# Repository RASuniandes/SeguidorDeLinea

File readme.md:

# Seguidor de linea
## Equipo 2024-1:
- Sergio Mora (SerAle25)
- Mateo López (Mateo-Lopez83)
- Alejandro Alvernia (AlejandroAAL)
- Laura Avelino (Lauraavelin)
- Valentina Romo ()
- Juan Felipe Ángulo (JuanFelipeAngulo)
- Mariana Vanoy (i4d1luc)
En rotación Valentina Arenas (Con interés de aprender temas de diseño mecánico e IMEC)

**Este es el equipo para 2024-1**

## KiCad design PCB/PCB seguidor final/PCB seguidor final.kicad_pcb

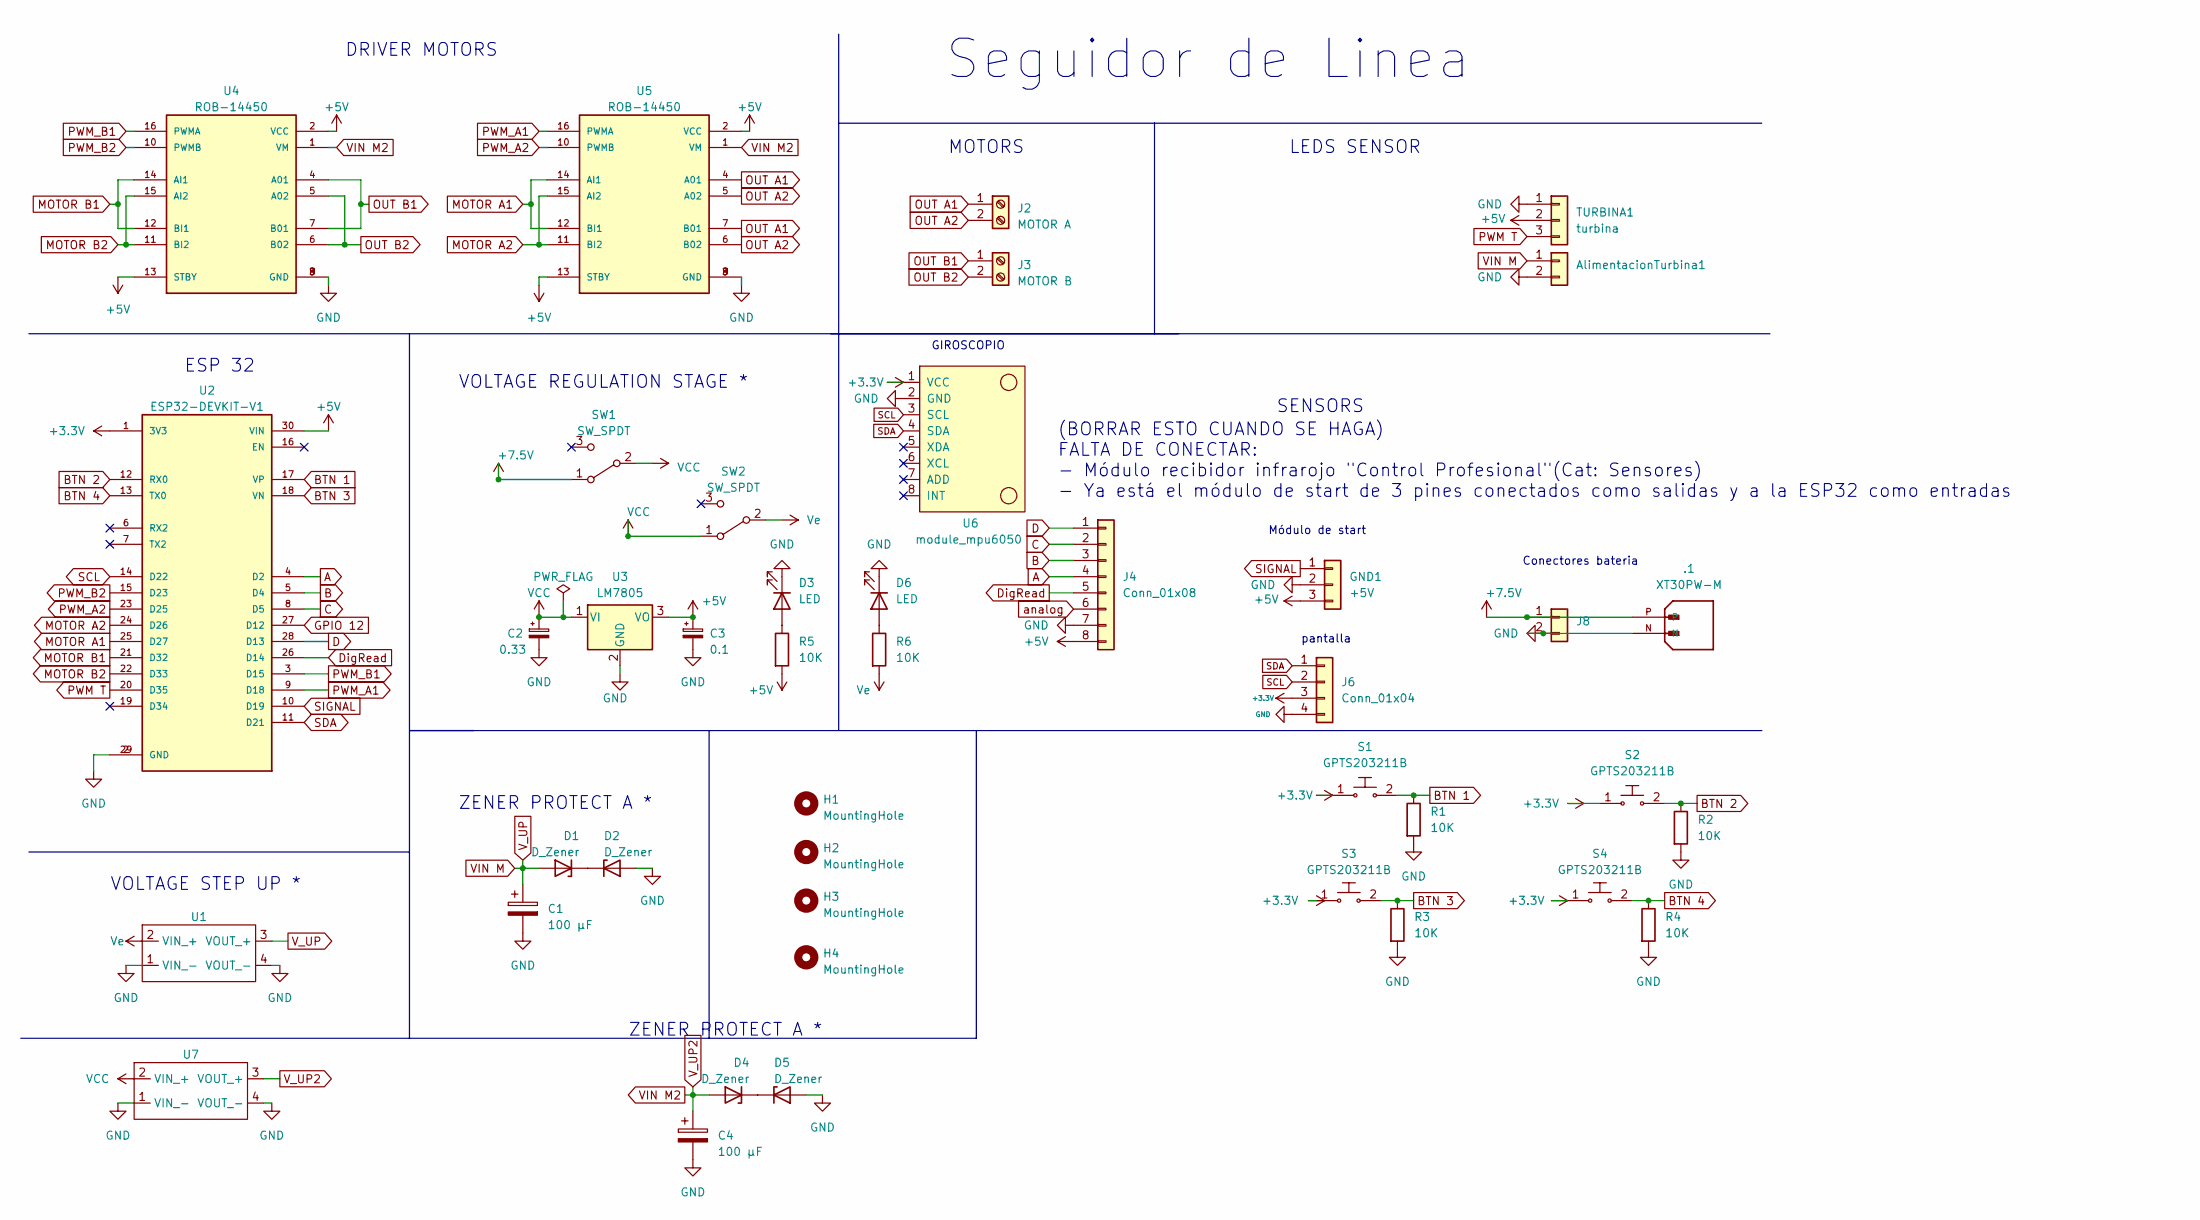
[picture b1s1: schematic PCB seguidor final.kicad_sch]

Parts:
.1: XT30PW-M; AMASS_XT30U-F_1x02_P5.0mm_Vertical; PARTREV 1.2
AlimentacionTurbina1: PinHeader_1x02_P2.54mm_Vertical
C1, C4: 100 μF; CP_Elec_6.3x5.9
C2: 0.33; CP_Elec_6.3x5.9
C3: 0.1; CP_Elec_6.3x5.9
D1, D2, D4, D5: D_Zener; D_A-405_P7.62mm_Horizontal
D3, D6: LED; LED_miniPLCC_2315_Handsoldering
GND1: +5V; PinHeader_1x03_P2.54mm_Vertical
H1, H2, H3, H4: MountingHole; MountingHole_3.2mm_M3_Pad_Via
J2: MOTOR A; TerminalBlock_4Ucon_1x02_P3.50mm_Horizontal
J3: MOTOR B; TerminalBlock_4Ucon_1x02_P3.50mm_Horizontal
J4: Conn_01x08; PinHeader_1x08_P2.54mm_Vertical
J6: Conn_01x04; 128x64OLED
J8: PinHeader_1x02_P2.54mm_Vertical
R1, R2, R3, R4, R5, R6: 10K; 0603
S1, S2, S3, S4: GPTS203211B; SW_PUSH_6mm_H5mm; MPN GPTS203211B
SW1, SW2: SW_SPDT; PinHeader_1x03_P2.54mm_Vertical
TURBINA1: turbina; PinHeader_1x03_P2.54mm_Vertical
U1, U7: MT3608-Module
U2: ESP32-DEVKIT-V1; MODULE_ESP32_DEVKIT_V1; PARTREV N/A
U3: LM7805; TO-252-2
U4, U5: ROB-14450; MODULE_ROB-14450; PARTREV 11-13-17
U6: module_mpu6050

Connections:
+3.3V: J6.3, S1.1, S2.1, S3.1, S4.1, U2.1 (3V3), U6.1 (VCC)
+5V: C3.1, GND1.3, J4.8, R5.2, TURBINA1.2, U2.30 (VIN), U3.3 (VO), U4.2 (VCC), U4.13 (STBY), U5.2 (VCC), U5.13 (STBY)
+7.5V: .1.P, J8.1, SW1.1 (A)
A: J4.4, U2.4 (D2)
B: J4.3, U2.5 (D4)
BTN 1: R1.1, S1.2, U2.17 (VP)
BTN 2: R2.1, S2.2, U2.12 (RX0)
BTN 3: R3.1, S3.2, U2.18 (VN)
BTN 4: R4.1, S4.2, U2.13 (TX0)
C: J4.2, U2.8 (D5)
D: J4.1, U2.28 (D13)
DigRead: J4.5, U2.26 (D14)
GND: .1.N, AlimentacionTurbina1.2, C1.2, C2.2, C3.2, C4.2, D2.2 (A), D3.1 (K), D5.2 (A), D6.1 (K), GND1.2, J4.7, J6.4, J8.2, R1.2, R2.2, R3.2, R4.2, TURBINA1.1, U1.1 (VIN_-), U1.4 (VOUT_-), U2.2 (GND), U2.29 (GND), U3.2 (GND), U4.3 (GND), U4.8 (GND), U4.9 (GND), U5.3 (GND), U5.8 (GND), U5.9 (GND), U6.2 (GND), U7.1 (VIN_-), U7.4 (VOUT_-)
GPIO 12: U2.27 (D12)
MOTOR A1: U2.25 (D27), U5.12 (BI1), U5.14 (AI1)
MOTOR A2: U2.24 (D26), U5.11 (BI2), U5.15 (AI2)
MOTOR B1: U2.21 (D32), U4.12 (BI1), U4.14 (AI1)
MOTOR B2: U2.22 (D33), U4.11 (BI2), U4.15 (AI2)
unnamed: D1.1 (K), D2.1 (K)
unnamed: D3.2 (A), R5.1
unnamed: D4.1 (K), D5.1 (K)
unnamed: D6.2 (A), R6.1
OUT A1: J2.1, U5.4 (A01), U5.7 (B01)
OUT A2: J2.2, U5.5 (A02), U5.6 (B02)
OUT B1: J3.1, U4.4 (A01), U4.7 (B01)
OUT B2: J3.2, U4.5 (A02), U4.6 (B02)
PWM T: TURBINA1.3, U2.20 (D35)
PWM_A1: U2.9 (D18), U5.16 (PWMA)
PWM_A2: U2.23 (D25), U5.10 (PWMB)
PWM_B1: U2.3 (D15), U4.16 (PWMA)
PWM_B2: U2.15 (D23), U4.10 (PWMB)
SCL: J6.2, U2.14 (D22), U6.3 (SCL)
SDA: J6.1, U2.11 (D21), U6.4 (SDA)
SIGNAL: GND1.1, U2.10 (D19)
VCC: C2.1, SW1.2 (B), SW2.1 (A), U3.1 (VI), U7.2 (VIN_+)
VIN M: AlimentacionTurbina1.1, C1.1, D1.2 (A), U1.3 (VOUT_+)
VIN M2: C4.1, D4.2 (A), U4.1 (VM), U5.1 (VM), U7.3 (VOUT_+)
Ve: R6.2, SW2.2 (B), U1.2 (VIN_+)
analog: J4.6

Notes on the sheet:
ZENER PROTECT A *
DRIVER MOTORS
Módulo de start
Seguidor de Linea
(BORRAR ESTO CUANDO SE HAGA) FALTA DE CONECTAR: - Módulo recibidor infrarojo "Control Profesional"(Cat: Sensores) - Ya está el módulo de start de 3 pines conectados como salidas y a la ESP32 como entradas
GIROSCOPIO
LEDS SENSOR
MOTORS
VOLTAGE STEP UP *
ESP 32
pantalla
SENSORS
Conectores bateria
VOLTAGE REGULATION STAGE *

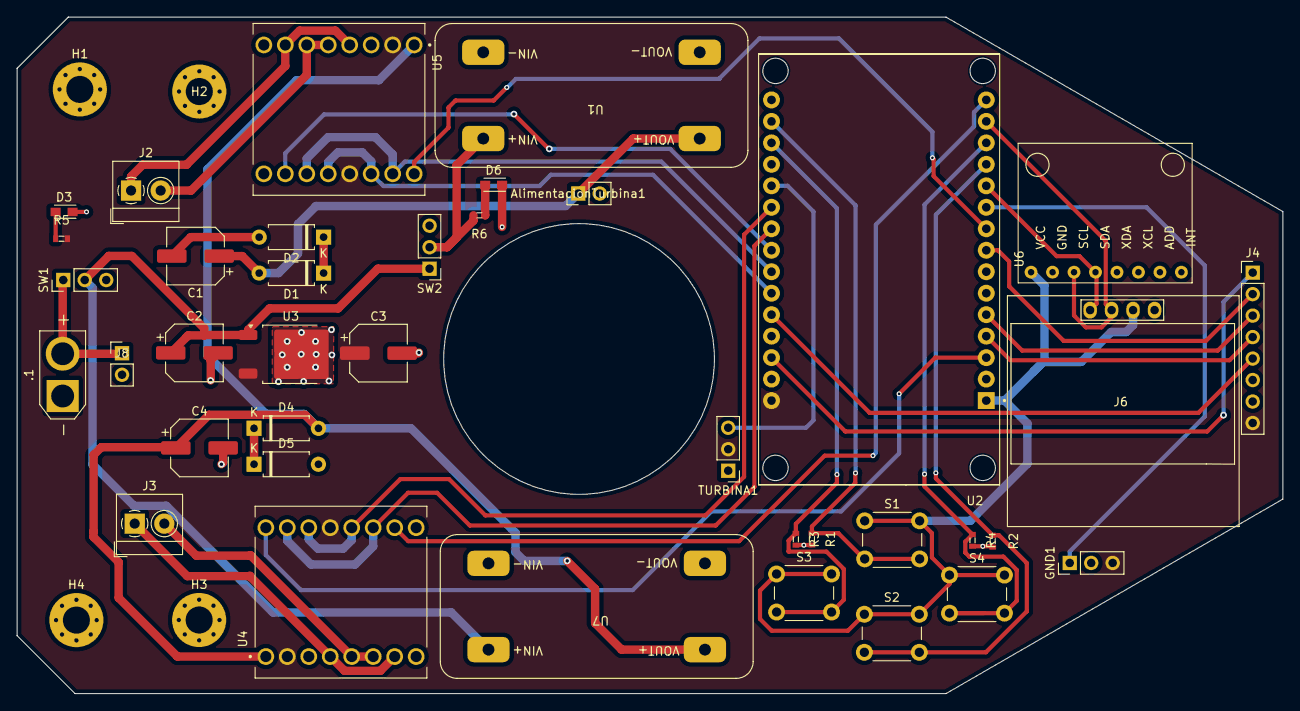
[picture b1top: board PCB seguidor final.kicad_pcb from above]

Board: 2 copper layers, 149.7 x 80.0 mm, 42 parts (0 on the bottom side), 37 nets.

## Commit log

2024-02-17 Primer Commit
2024-02-20 Nuevos miebros agregados readme.md
2024-02-20 Usuario - Update readme.md
2024-02-21 CAmbios del equiipo de mariana para desarrollo PCB
2024-02-23 Puse un punto
2024-02-23 Update Seguidor de linea.kicad_sch
    creo que ya
2024-02-23 Ping Pong
    Ping Pong Tutorial GH
2024-02-23 Epico
2024-02-23 Segundo Driver de motor añadido
    -Termine lo del segundo driver de motor
    -Acomode el esquema
2024-02-23 Módulo start
    Agregué el módulo de start a sensors, con un total de 3 pines para signal, VCC y Gnd
2024-03-01 xd
    xd
2024-03-08 Add files via upload
    este es el archivo más actualizado para la pcb, se irá trabajando sobre este. Es necesario completar con los componentes que hagan falta e ir agregando las respectivas huellas para cada uno
2024-03-12 Create Seguidor de línea final
2024-04-02 intento lector regleta
2024-04-03 Ejemplo
2024-04-05 tal vez funciona (?)
2024-04-05 cambios al fin lee algo yay
2024-04-16 Porfin trato de hacer algo xd
2024-04-16 librerias
2024-04-16 mas librerias
2024-04-16 las huellas FUNCIONAN
2024-04-16 avance
2024-04-17 Acabada(esperando corrección)
2024-04-17 Algunas correcciones hechas
    Flata poner led de encendido general y turbina, hacerla un poco mas estetica
2024-04-19 Correcciones hechas
2024-04-23 lector funcional
